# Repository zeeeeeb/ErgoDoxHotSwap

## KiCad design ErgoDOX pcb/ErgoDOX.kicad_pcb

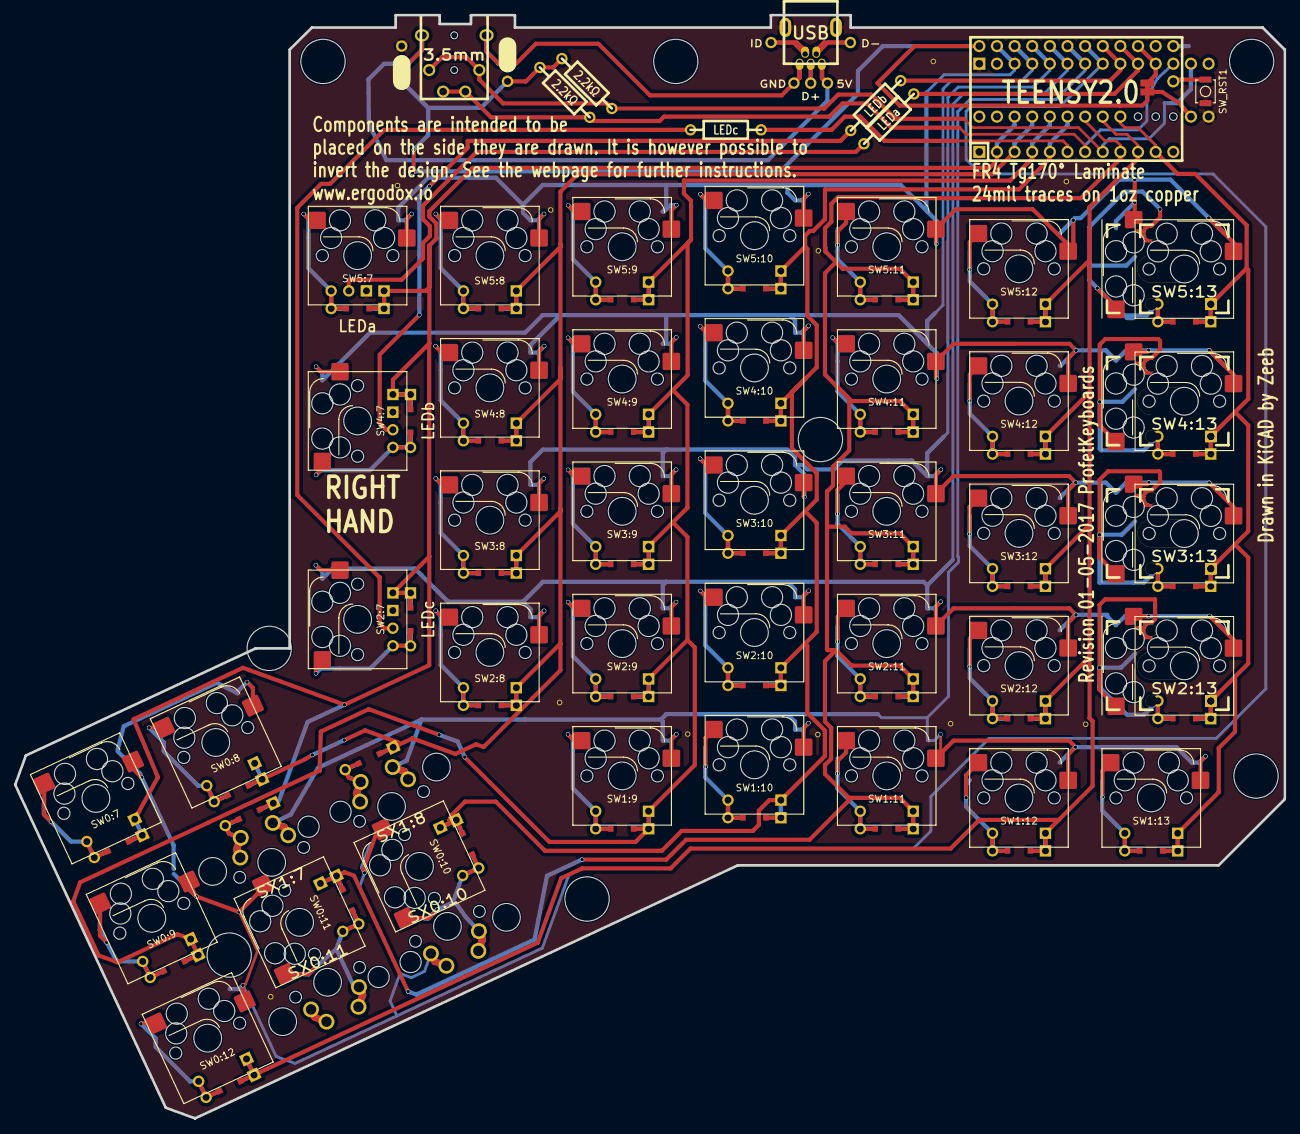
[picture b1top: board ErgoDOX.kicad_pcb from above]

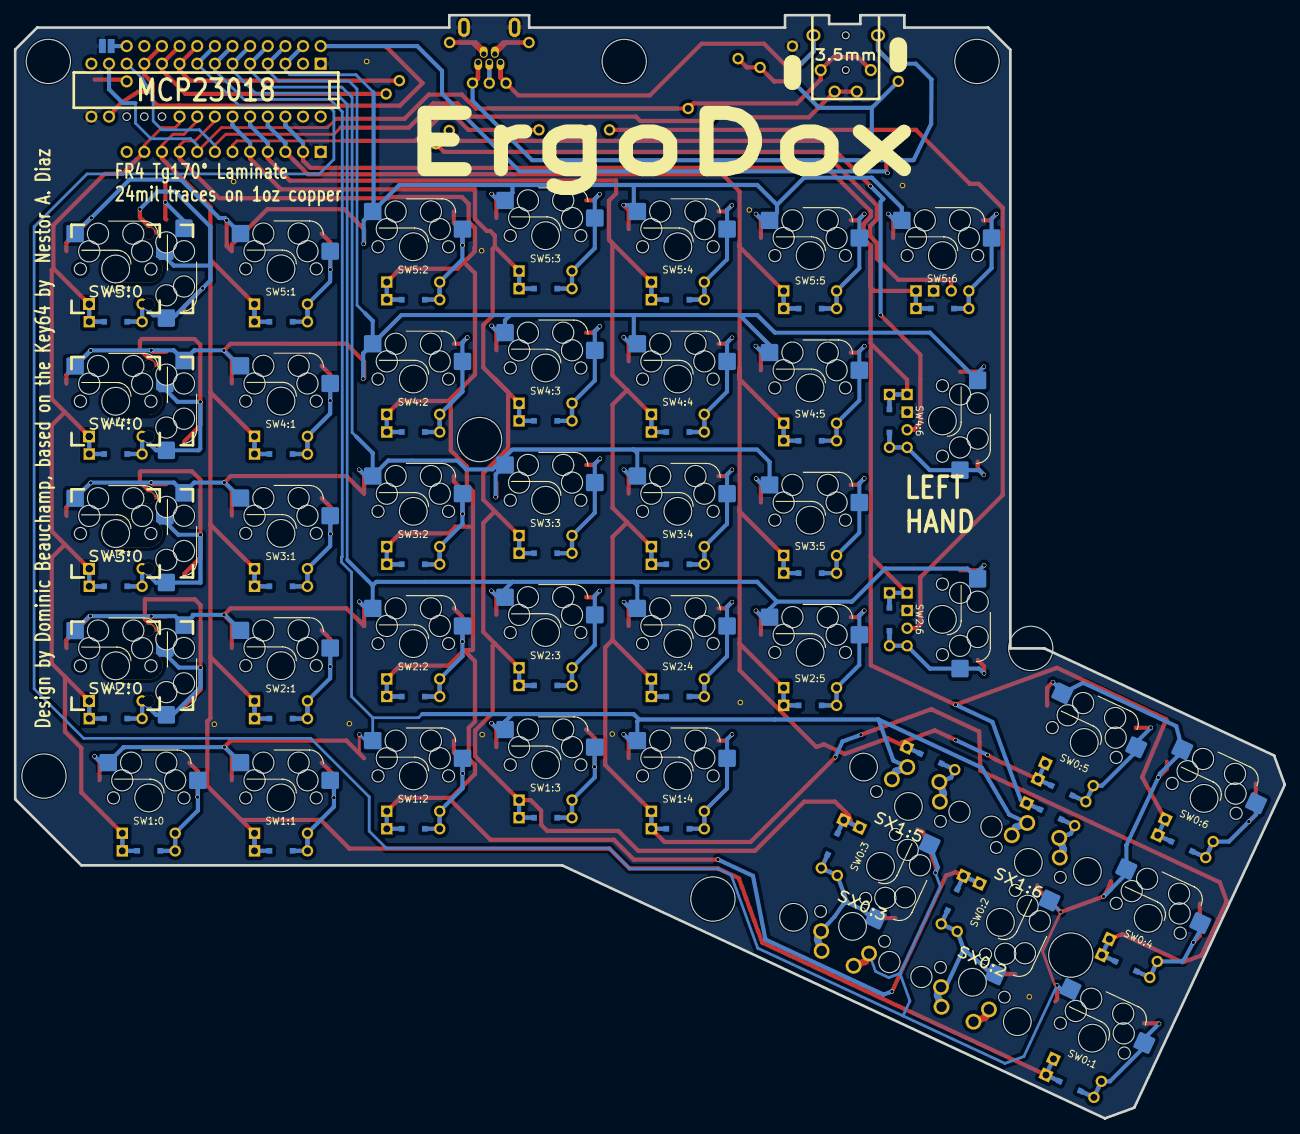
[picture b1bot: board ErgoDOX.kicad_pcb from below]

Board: 2 copper layers, 182.8 x 158.9 mm, 75 parts (3 on the bottom side), 66 nets.

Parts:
D1:7, D1:8: D; DIODE
H99: MECHANICAL; ErgoDOXmech
J1: USB; USBMINImod
J2: 3.5mm; 4pin35mmAudio
J3, J4: JMP; 100PITCH1X3
JP1, JP2: JUMPER; GAP
LED_A1: LEDa; MX_LED
LED_B1: LEDb; MX_LED
LED_C1: LEDc; MX_LED
R1, R2: 2.2kΩ; RESISTOR
RA1: LEDa; RESISTOR
RB1: LEDb; RESISTOR
RC1: LEDc; RESISTOR
S1, S2: STAB200; STAB_PCB940
STITCHING_VIA: STITCHING_VIA
STITCHING_VIA#2, STITCHING_VIA#3, STITCHING_VIA#4, STITCHING_VIA#5, STITCHING_VIA#6, STITCHING_VIA#7, STITCHING_VIA#8, STITCHING_VIA#9, STITCHING_VIA#10, STITCHING_VIA#11: STITCHING_VIA
SW0:7: SW0:6; SW_Hotswap_Kailh_MX
SW0:8: SW0:5; SW_Hotswap_Kailh_MX
SW0:9: SW0:4; SW_Hotswap_Kailh_MX
SW0:10: SW0:3; SW_Hotswap_Kailh_MX
SW0:11: SW0:2; SW_Hotswap_Kailh_MX
SW0:12: SW0:1; SW_Hotswap_Kailh_MX
SW1:9: SW1:4; SW_Hotswap_Kailh_MX
SW1:10: SW1:3; SW_Hotswap_Kailh_MX
SW1:11: SW1:2; SW_Hotswap_Kailh_MX
SW1:12: SW1:1; SW_Hotswap_Kailh_MX
SW1:13: SW1:0; SW_Hotswap_Kailh_MX
SW2:7: SW2:6; SW_Hotswap_Kailh_MX
SW2:8: SW2:5; SW_Hotswap_Kailh_MX
SW2:9: SW2:4; SW_Hotswap_Kailh_MX
SW2:10: SW2:3; SW_Hotswap_Kailh_MX
SW2:11: SW2:2; SW_Hotswap_Kailh_MX
SW2:12: SW2:1; SW_Hotswap_Kailh_MX
SW2:13: SW2:0; MX_FLIP_HOTSWAP
SW3:8: SW3:5; SW_Hotswap_Kailh_MX
SW3:9: SW3:4; SW_Hotswap_Kailh_MX
SW3:10: SW3:3; SW_Hotswap_Kailh_MX
SW3:11: SW3:2; SW_Hotswap_Kailh_MX
SW3:12: SW3:1; SW_Hotswap_Kailh_MX
SW3:13: SW3:0; MX_FLIP_HOTSWAP
SW4:7: SW4:6; SW_Hotswap_Kailh_MX
SW4:8: SW4:5; SW_Hotswap_Kailh_MX
SW4:9: SW4:4; SW_Hotswap_Kailh_MX
SW4:10: SW4:3; SW_Hotswap_Kailh_MX
SW4:11: SW4:2; SW_Hotswap_Kailh_MX
SW4:12: SW4:1; SW_Hotswap_Kailh_MX
SW4:13: SW4:0; MX_FLIP_HOTSWAP
SW5:7: SW5:6; SW_Hotswap_Kailh_MX
SW5:8: SW5:5; SW_Hotswap_Kailh_MX
SW5:9: SW5:4; SW_Hotswap_Kailh_MX
SW5:10: SW5:3; SW_Hotswap_Kailh_MX
SW5:11: SW5:2; SW_Hotswap_Kailh_MX
SW5:12: SW5:1; SW_Hotswap_Kailh_MX
SW5:13: SW5:0; MX_FLIP_HOTSWAP
SW_RST1: SWITCH_PUSH; SW_SPST_B3U-1000P
SX0:10: SX0:3; MX_FLIP
SX0:11: SX0:2; MX_FLIP
SX1:7: SX1:6; MX_FLIP
SX1:8: SX1:5; MX_FLIP
U1: TEENSY2.0; TEENSY_2.0_WITH_RESET
U2: MCP23018; DIP28_300

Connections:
/COL0: SW1:13.4, SW2:13.4, SW3:13.4, SW4:13.4, SW5:13.4, U1.11, U2.20
/COL1: SW0:12.4, SW1:12.4, SW2:12.4, SW3:12.4, SW4:12.4, SW5:12.4, U1.10, U2.21
/COL4: SW0:9.4, SW1:9.4, SW2:9.4, SW3:9.4, SW4:9.4, SW5:9.4, U1.4, U2.24
/COL5: D1:8.2, SW0:8.4, SW2:8.4, SW3:8.4, SW4:8.4, SW5:8.4, U1.3, U2.25
/COL6: D1:7.2, SW0:7.4, SW2:7.4, SW4:7.4, SW5:7.4, U1.2, U2.26
/COL10: SW0:10.4, SW1:10.4, SW2:10.4, SW3:10.4, SW4:10.4, SW5:10.4, U1.5, U2.23
/COL11: SW0:11.4, SW1:11.4, SW2:11.4, SW3:11.4, SW4:11.4, SW5:11.4, U1.9, U2.22
/LED_A: RA1.1, U1.21, U2.10
/LED_B: RB1.1, U1.22, U2.9
/LED_C: RC1.1, U1.6
/ROW0: SW0:7.1, SW0:8.1, SW0:9.1, SW0:10.1, SW0:11.1, SW0:12.1, SX0:10.1, SX0:11.1, U1.23, U2.8
/ROW1: SW1:9.1, SW1:10.1, SW1:11.1, SW1:12.1, SW1:13.1, SX1:7.1, SX1:8.1, U1.24, U2.7
/ROW2: SW2:7.1, SW2:8.1, SW2:9.1, SW2:10.1, SW2:11.1, SW2:12.1, SW2:13.1, SW2:13.2, U1.25, U2.6
/ROW3: SW3:8.1, SW3:9.1, SW3:10.1, SW3:11.1, SW3:12.1, SW3:13.1, SW3:13.2, U1.26, U2.5
/ROW4: SW4:7.1, SW4:8.1, SW4:9.1, SW4:10.1, SW4:11.1, SW4:12.1, SW4:13.1, SW4:13.2, U1.27, U2.4
/ROW5: SW5:7.1, SW5:8.1, SW5:9.1, SW5:10.1, SW5:11.1, SW5:12.1, SW5:13.1, SW5:13.2, U1.28, U2.3
/RST: SW_RST1.1, U1.16
/SCLM: J2.3, J2.5, R2.2, U1.7, U2.12
/SDAM: J2.2, J2.6, R1.2, U1.8, U2.13
GND: J1.6, J3.3, J4.3, JP2.1, LED_A1.2, LED_B1.2, LED_C1.2, STITCHING_VIA.GND, STITCHING_VIA#2.GND, STITCHING_VIA#3.GND, STITCHING_VIA#4.GND, STITCHING_VIA#5.GND, STITCHING_VIA#6.GND, STITCHING_VIA#7.GND, STITCHING_VIA#8.GND, STITCHING_VIA#9.GND, STITCHING_VIA#10.GND, STITCHING_VIA#11.GND, SW_RST1.2, U1.1, U1.18, U2.1, U2.15
unnamed: D1:7.1, SX1:7.2
unnamed: D1:8.1, SX1:8.2
unnamed: J1.1, J2.4, J4.2
unnamed: J1.5, J2.1, J3.2
unnamed: LED_A1.1, RA1.2
unnamed: LED_B1.1, RB1.2
unnamed: LED_C1.1, RC1.2
unnamed: SW0:7.2, SW0:7.3
unnamed: SW0:8.2, SW0:8.3
unnamed: SW0:9.2, SW0:9.3
unnamed: SW0:10.2, SW0:10.3, SX0:10.2
unnamed: SW0:11.2, SW0:11.3, SX0:11.2
unnamed: SW0:12.2, SW0:12.3
unnamed: SW1:9.2, SW1:9.3
unnamed: SW1:10.2, SW1:10.3
unnamed: SW1:11.2, SW1:11.3
unnamed: SW1:12.2, SW1:12.3
unnamed: SW1:13.2, SW1:13.3
unnamed: SW2:7.2, SW2:7.3
unnamed: SW2:8.2, SW2:8.3
unnamed: SW2:9.2, SW2:9.3
unnamed: SW2:10.2, SW2:10.3
unnamed: SW2:11.2, SW2:11.3
unnamed: SW2:12.2, SW2:12.3
unnamed: SW2:13.1, SW2:13.2, SW2:13.3
unnamed: SW3:8.2, SW3:8.3
unnamed: SW3:9.2, SW3:9.3
unnamed: SW3:10.2, SW3:10.3
unnamed: SW3:11.2, SW3:11.3
unnamed: SW3:12.2, SW3:12.3
unnamed: SW3:13.1, SW3:13.2, SW3:13.3
unnamed: SW4:7.2, SW4:7.3
unnamed: SW4:8.2, SW4:8.3
unnamed: SW4:9.2, SW4:9.3
unnamed: SW4:10.2, SW4:10.3
unnamed: SW4:11.2, SW4:11.3
unnamed: SW4:12.2, SW4:12.3
unnamed: SW4:13.1, SW4:13.2, SW4:13.3
unnamed: SW5:7.2, SW5:7.3
unnamed: SW5:8.2, SW5:8.3
unnamed: SW5:9.2, SW5:9.3
unnamed: SW5:10.2, SW5:10.3
unnamed: SW5:11.2, SW5:11.3
unnamed: SW5:12.2, SW5:12.3
unnamed: SW5:13.1, SW5:13.2, SW5:13.3
VCC: J3.1, J4.1, JP1.1, R1.1, R2.1, U1.20, U1.29, U2.11, U2.16

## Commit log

2016-12-06 Fixes
2016-12-07 Repo cleanup
2017-01-06 Adding support for reversible female USB Port and optional reset switch. This will allow the right hand of the Ergodox to be flipped and used as the left hand. In this scenario the teensy should be s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
    Reset switch part number: OMRON B3U-1000P
2018-01-28 Fixing all loops in all dxf files
    Almost all DXF files had some loops in it (lines or dots that were not connected to anything else). That was a problem, as most laser cutter will act weirdly because of that.
    Fixing this allow laser cutter to do the cut in one smooth line, and not try to leave some very close gaps because some dots were not connected.
    Files were imported then exported using Fusion 360. It seems that they have been vastly re-written, but as the DXF format has been invented by Autodesk, it should be ok and readable by other CAD soft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
    You can see an example of the loops in one file here : https://imgur.com/zZA2Odz
    This is checked using an addin called Sketch Checker in
2018-09-24 [case] Fix right hand size
    Right hand was 10 times bigger than left hand.
    Also replaces commas by dots as decimal separator.
2018-10-13 [case] Fix right hand scale
2024-06-01 some progress
